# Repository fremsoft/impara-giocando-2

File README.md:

# impara-giocando-2
Seconda stagione di impara giocando, laboratorio di robotica e meccatronica
 
In questa directory verrà caricato tutto il materiale didattico che sviluppiamo nel corso del  laboratorio di robotica e meccatronica «impara giocando»

La playlist completa è disponibile in abbonamento a questo link: [Laboratorio di Robotica e Meccatronica](https://www.youtube.com/playlist?list=PLxAafib4pWc7ZTqss_0A76ByotfsSOVeD)

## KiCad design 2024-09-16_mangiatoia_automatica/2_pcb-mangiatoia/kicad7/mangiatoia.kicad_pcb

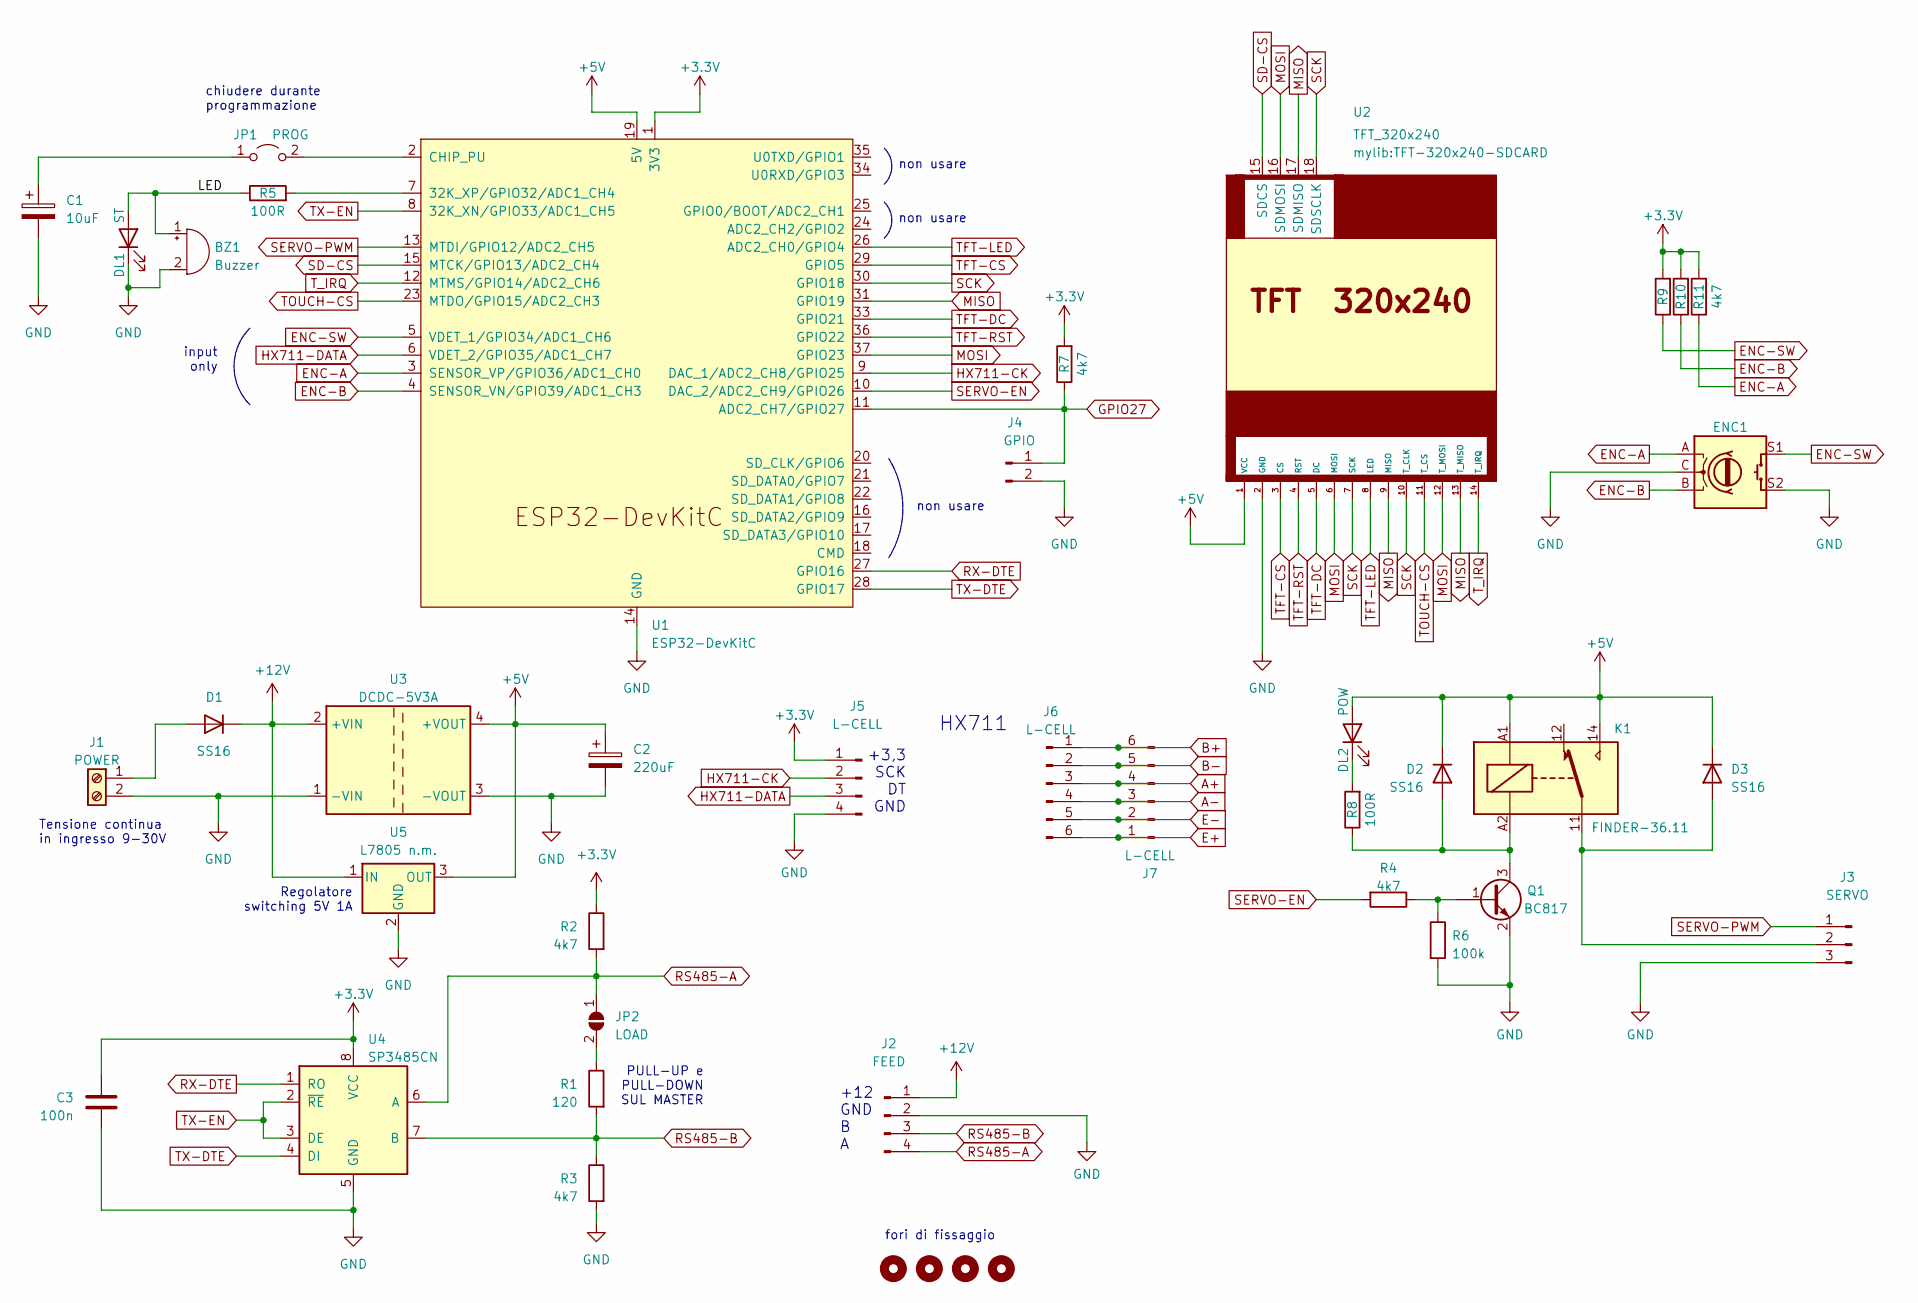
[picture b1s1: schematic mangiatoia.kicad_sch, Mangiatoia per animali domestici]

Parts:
BZ1: Buzzer; Buzzer_12x9.5RM7.6
C1: 10uF; CP_Radial_D6.3mm_P2.50mm
C2: 220uF; CP_Radial_D10.0mm_P5.00mm
C3: 100n; C_0603_1608Metric
D1, D2, D3: SS16; D_SMA
DL1: ST; LED_D5.0mm
DL2: POW; LED_0805_2012Metric
ENC1: RotaryEncoder_Switch; RotaryEncoder_Alps_EC11E-Switch_Vertical_H20mm
H1, H2, H3, H4: MountingHole; MountingHole_4.3mm_M4
J1: POWER; PhoenixContact_MSTBA_2,5_2-G-5,08_1x02_P5.08mm_Horizontal
J2: FEED; PinHeader_1x04_P2.54mm_Vertical
J3: SERVO; PinHeader_1x03_P2.54mm_Vertical
J4: GPIO; PinHeader_1x02_P2.54mm_Vertical
J5: L-CELL; PinHeader_1x04_P2.54mm_Vertical
J6: L-CELL; PinHeader_1x06_P2.54mm_Vertical
J7: L-CELL; TBL002A-350-06GR-2OR
JP1: PROG; PinHeader_1x02_P2.54mm_Vertical
JP2: LOAD; SolderJumper-2_P1.3mm_Open_RoundedPad1.0x1.5mm
K1: FINDER-36.11; Relay_SPDT_Finder_36.11
Q1: BC817; SOT-23
R1: 120; R_1206_3216Metric
R2, R3, R4: 4k7; R_0805_2012Metric; JLCPCB C304777
R5, R8: 100R; R_0805_2012Metric
R6: 100k; R_0805_2012Metric; JLCPCB C304777
R7, R9, R10, R11: 4k7; R_0805_2012Metric
U1: ESP32-DevKitC
U2: TFT_320x240; TFT-320x240-SDCARD
U3: DCDC-5V3A
U4: SP3485CN; SOIC-8_3.9x4.9mm_P1.27mm
U5: L7805 n.m.; TO-220-3_Vertical

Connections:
+3.3V: C3.1, J5.1, R2.1, R7.2, R9.2, R10.2, R11.2, U1.1 (3V3), U4.8 (VCC)
+5V: C2.1, D2.1 (K), D3.1 (K), DL2.2 (A), K1.14, K1.A1, U1.19 (5V), U2.1 (VCC), U3.4 (+VOUT), U5.3 (OUT)
+12V: D1.1 (K), J2.1, U3.2 (+VIN), U5.1 (IN)
/LED: BZ1.1 (-), DL1.2 (A), R5.1
A+: J6.3, J7.4
A-: J6.4, J7.3
B+: J6.1, J7.6
B-: J6.2, J7.5
E+: J6.6, J7.1
E-: J6.5, J7.2
ENC-A: ENC1.A, R11.1, U1.3 (SENSOR_VP/GPIO36/ADC1_CH0)
ENC-B: ENC1.B, R10.1, U1.4 (SENSOR_VN/GPIO39/ADC1_CH3)
ENC-SW: ENC1.S1, R9.1, U1.5 (VDET_1/GPIO34/ADC1_CH6)
GND: BZ1.2 (+), C1.2, C2.2, C3.2, DL1.1 (K), ENC1.C, ENC1.S2, J1.2, J2.2, J3.3, J4.2, J5.4, Q1.2 (E), R3.2, R6.2, U1.14 (GND), U1.32 (GND), U1.38 (GND), U2.2 (GND), U3.1 (-VIN), U3.3 (-VOUT), U4.5 (GND), U5.2 (GND)
GPIO27: J4.1, R7.1, U1.11 (ADC2_CH7/GPIO27)
HX711-CK: J5.2, U1.9 (DAC_1/ADC2_CH8/GPIO25)
HX711-DATA: J5.3, U1.6 (VDET_2/GPIO35/ADC1_CH7)
MISO: U1.31 (GPIO19), U2.9 (MISO), U2.13 (T_MISO), U2.17 (SDMISO)
MOSI: U1.37 (GPIO23), U2.6 (MOSI), U2.12 (T_MOSI), U2.16 (SDMOSI)
unnamed: D1.2 (A), J1.1
unnamed: D2.2 (A), K1.A2, Q1.3 (C), R8.1
unnamed: D3.2 (A), J3.2, K1.11
unnamed: DL2.1 (K), R8.2
unnamed: C1.1, JP1.1 (A)
unnamed: JP1.2 (B), U1.2 (CHIP_PU)
unnamed: JP2.2 (B), R1.1
unnamed: Q1.1 (B), R4.1, R6.1
unnamed: R5.2, U1.7 (32K_XP/GPIO32/ADC1_CH4)
RS485-A: J2.4, JP2.1 (A), R2.2, U4.6 (A)
RS485-B: J2.3, R1.2, R3.1, U4.7 (B)
RX-DTE: U1.27 (GPIO16), U4.1 (RO)
SCK: U1.30 (GPIO18), U2.7 (SCK), U2.10 (T_CLK), U2.18 (SDSCLK)
SD-CS: U1.15 (MTCK/GPIO13/ADC2_CH4), U2.15 (SDCS)
SERVO-EN: R4.2, U1.10 (DAC_2/ADC2_CH9/GPIO26)
SERVO-PWM: J3.1, U1.13 (MTDI/GPIO12/ADC2_CH5)
TFT-CS: U1.29 (GPIO5), U2.3 (CS)
TFT-DC: U1.33 (GPIO21), U2.5 (DC)
TFT-LED: U1.26 (ADC2_CH0/GPIO4), U2.8 (LED)
TFT-RST: U1.36 (GPIO22), U2.4 (RST)
TOUCH-CS: U1.23 (MTDO/GPIO15/ADC2_CH3), U2.11 (T_CS)
TX-DTE: U1.28 (GPIO17), U4.4 (DI)
TX-EN: U1.8 (32K_XN/GPIO33/ADC1_CH5), U4.2 (~RE), U4.3 (DE)
T_IRQ: U1.12 (MTMS/GPIO14/ADC2_CH6), U2.14 (T_IRQ)

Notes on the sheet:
chiudere durante programmazione
+3,3 SCK DT GND
PULL-UP e PULL-DOWN SUL MASTER
non usare
+12 GND B A
HX711
input only
Regolatore switching 5V 1A
Tensione continua in ingresso 9-30V
fori di fissaggio

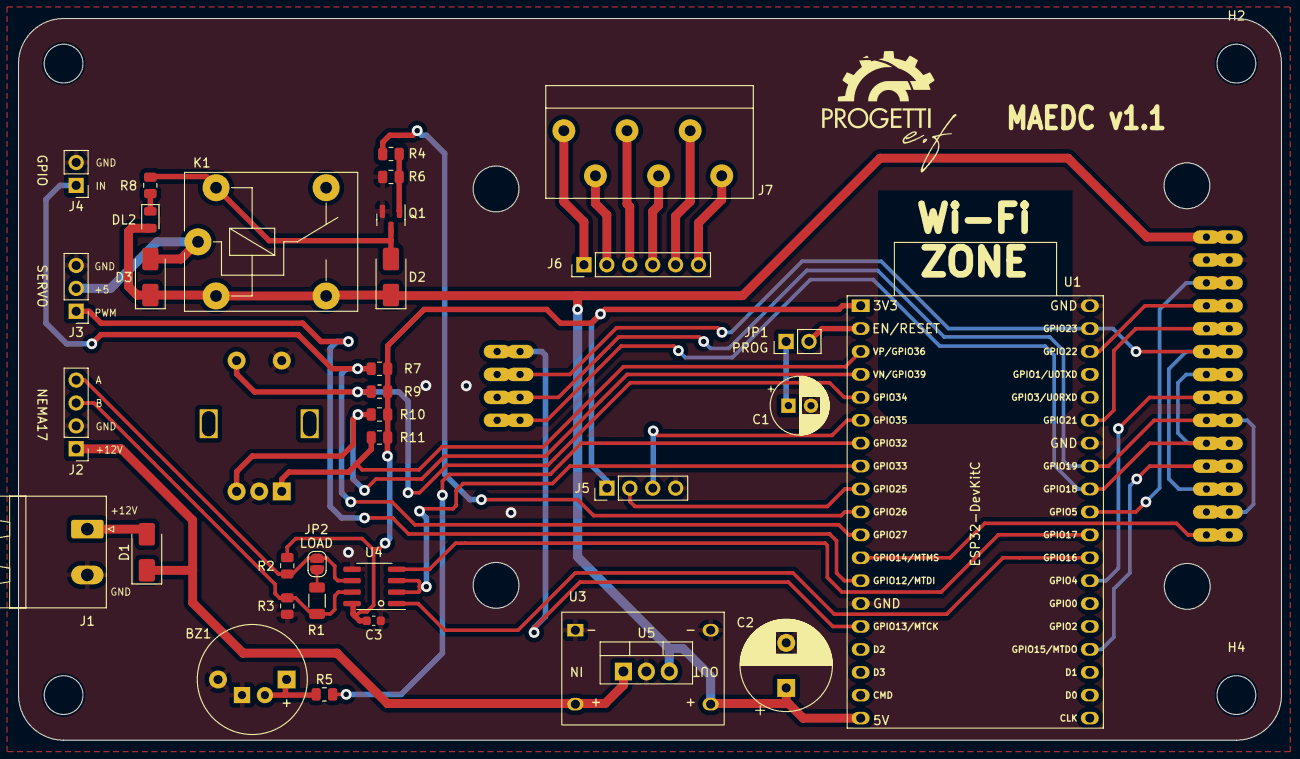
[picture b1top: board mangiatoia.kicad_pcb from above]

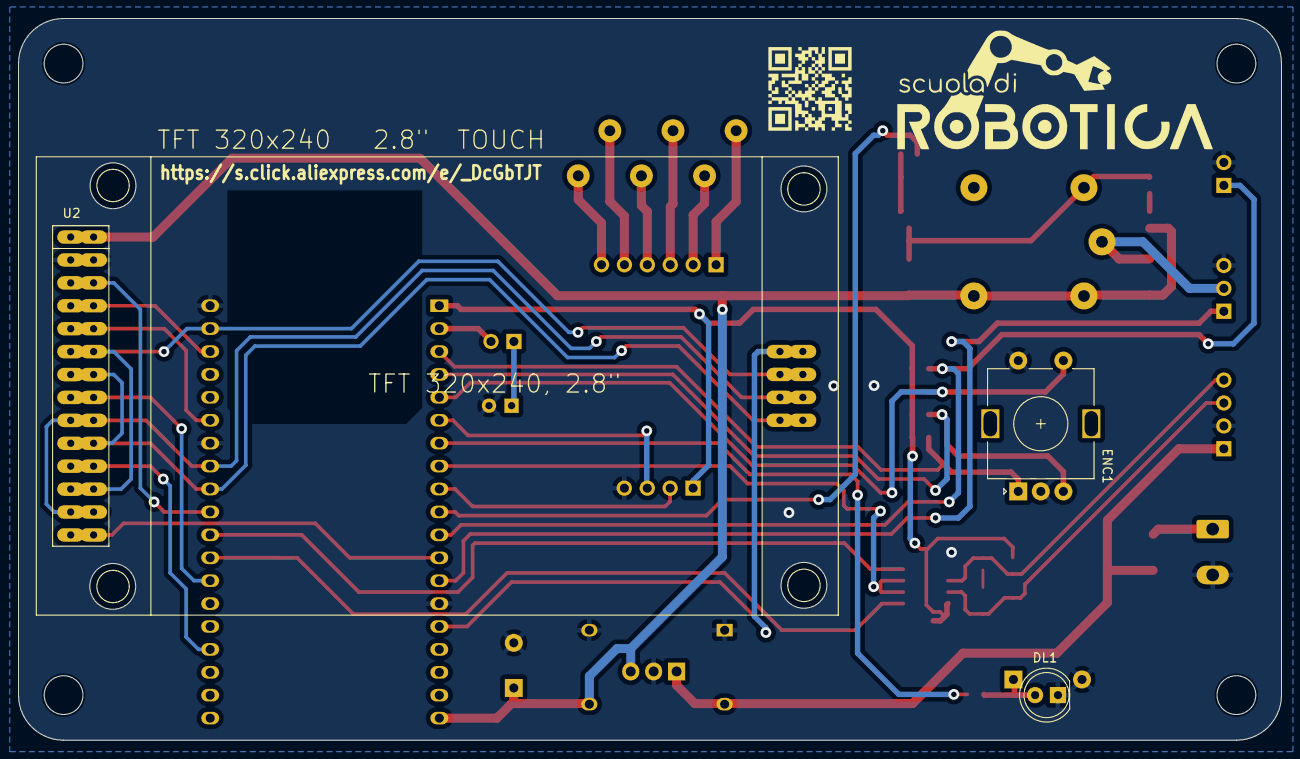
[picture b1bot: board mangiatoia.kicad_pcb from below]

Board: 2 copper layers, 140.0 x 80.0 mm, 41 parts (3 on the bottom side), 43 nets.

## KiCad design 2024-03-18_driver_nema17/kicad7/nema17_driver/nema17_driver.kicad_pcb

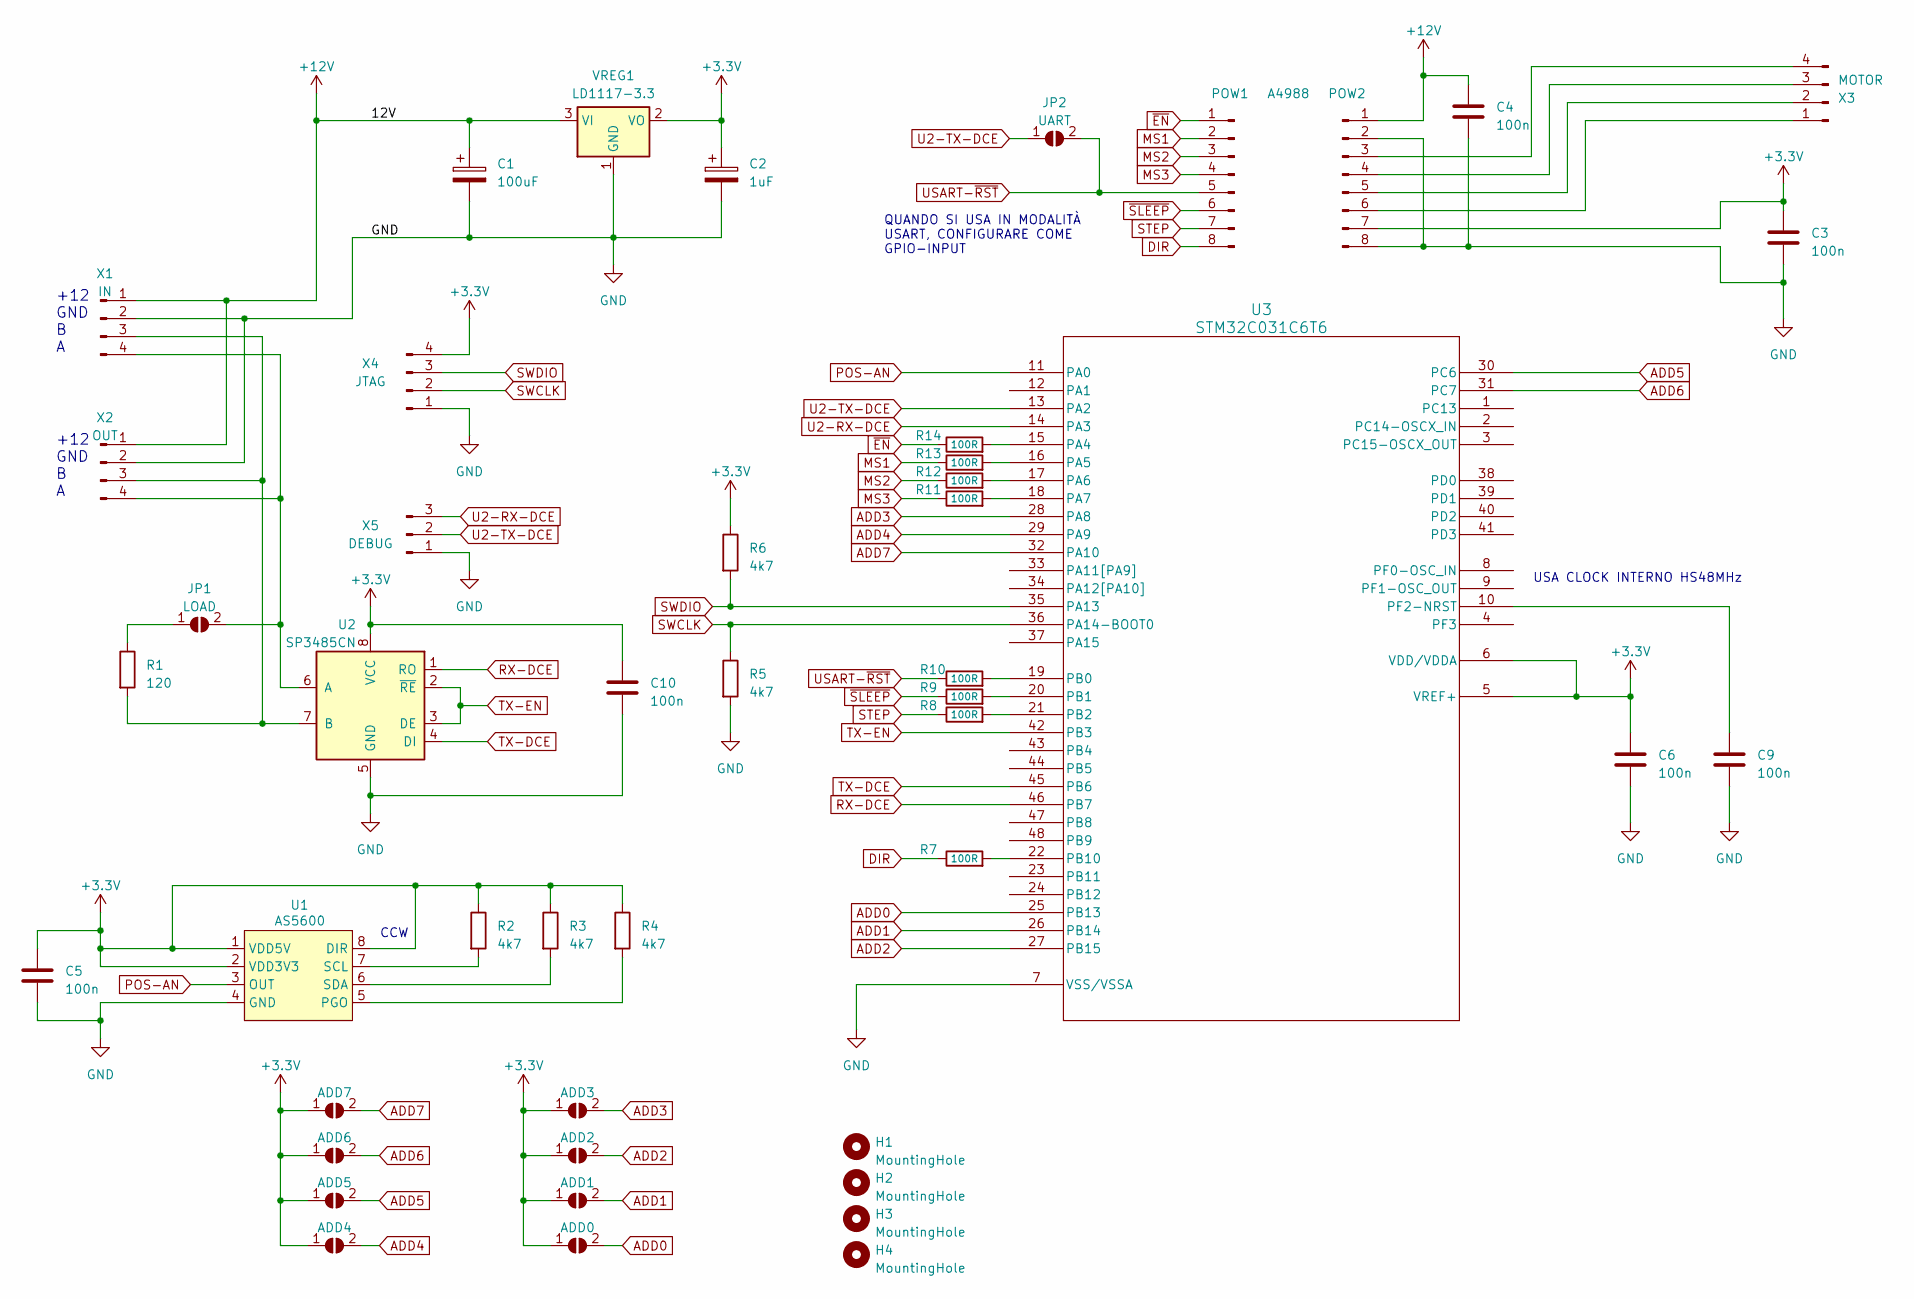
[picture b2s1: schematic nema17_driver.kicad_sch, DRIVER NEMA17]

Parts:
C1: 100uF; CP_Elec_6.3x7.7
C2: 1uF; CP_Elec_4x5.3
C3, C4, C5, C6, C9, C10: 100n; C_0603_1608Metric
H1, H2, H3, H4: MountingHole; MountingHole_3.5mm
JP1: LOAD; SolderJumper-2_P1.3mm_Open_RoundedPad1.0x1.5mm
JP2: UART; SolderJumper-2_P1.3mm_Open_RoundedPad1.0x1.5mm
JP3: ADD7; SolderJumper-2_P1.3mm_Open_RoundedPad1.0x1.5mm
JP4: ADD6; SolderJumper-2_P1.3mm_Open_RoundedPad1.0x1.5mm
JP5: ADD5; SolderJumper-2_P1.3mm_Open_RoundedPad1.0x1.5mm
JP6: ADD4; SolderJumper-2_P1.3mm_Open_RoundedPad1.0x1.5mm
JP7: ADD3; SolderJumper-2_P1.3mm_Open_RoundedPad1.0x1.5mm
JP8: ADD2; SolderJumper-2_P1.3mm_Open_RoundedPad1.0x1.5mm
JP9: ADD1; SolderJumper-2_P1.3mm_Open_RoundedPad1.0x1.5mm
JP10: ADD0; SolderJumper-2_P1.3mm_Open_RoundedPad1.0x1.5mm
POW1: A4988; PinSocket_1x08_P2.54mm_Vertical
POW2: Conn_01x08_Pin; PinSocket_1x08_P2.54mm_Vertical
R1: 120; R_1206_3216Metric
R2, R3, R4, R5, R6: 4k7; R_0603_1608Metric
R7, R8, R9, R10, R11, R12, R13, R14: 100R; R_0603_1608Metric
U1: AS5600; SO-8_3.9x4.9mm_P1.27mm
U2: SP3485CN; SOIC-8_3.9x4.9mm_P1.27mm
U3: STM32C031C6T6; LQFP48-7x7mm_STM
VREG1: LD1117-3.3; SOT-223-3_TabPin2
X1: IN; PinHeader_1x04_P2.54mm_Vertical
X2: OUT; PinHeader_1x04_P2.54mm_Vertical
X3: MOTOR; TBL002A-350-04GR-2OR
X4: JTAG; PinHeader_1x04_P2.54mm_Vertical
X5: DEBUG; PinHeader_1x03_P2.54mm_Vertical

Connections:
+3.3V: C2.1, C3.1, C5.1, C6.1, C10.1, JP3.1 (A), JP4.1 (A), JP5.1 (A), JP6.1 (A), JP7.1 (A), JP8.1 (A), JP9.1 (A), JP10.1 (A), POW2.7, R2.1, R3.1, R4.1, R6.1, U1.1 (VDD5V), U1.2 (VDD3V3), U1.8 (DIR), U2.8 (VCC), U3.5 (VREF+), U3.6 (VDD/VDDA), VREG1.2 (VO), X4.4
+12V: C1.1, C4.1, POW2.1, VREG1.3 (VI), X1.1, X2.1
ADD0: JP10.2 (B), U3.25 (PB13)
ADD1: JP9.2 (B), U3.26 (PB14)
ADD2: JP8.2 (B), U3.27 (PB15)
ADD3: JP7.2 (B), U3.28 (PA8)
ADD4: JP6.2 (B), U3.29 (PA9)
ADD5: JP5.2 (B), U3.30 (PC6)
ADD6: JP4.2 (B), U3.31 (PC7)
ADD7: JP3.2 (B), U3.32 (PA10)
DIR: POW1.8, R7.1
GND: C1.2, C2.2, C3.2, C4.2, C5.2, C6.2, C9.2, C10.2, POW2.2, POW2.8, R5.2, U1.4 (GND), U2.5 (GND), U3.7 (VSS/VSSA), VREG1.1 (GND), X1.2, X2.2, X4.1, X5.1
MS1: POW1.2, R13.1
MS2: POW1.3, R12.1
MS3: POW1.4, R11.1
unnamed: JP1.1 (A), R1.1
unnamed: JP1.2 (B), U2.6 (A), X1.4, X2.4
unnamed: POW2.3, X3.4
unnamed: POW2.4, X3.3
unnamed: POW2.5, X3.2
unnamed: POW2.6, X3.1
unnamed: R4.2, U1.5 (PGO)
unnamed: R2.2, U1.7 (SCL)
unnamed: R3.2, U1.6 (SDA)
unnamed: R1.2, U2.7 (B), X1.3, X2.3
unnamed: R14.2, U3.15 (PA4)
unnamed: R13.2, U3.16 (PA5)
unnamed: R12.2, U3.17 (PA6)
unnamed: R11.2, U3.18 (PA7)
unnamed: R10.2, U3.19 (PB0)
unnamed: R9.2, U3.20 (PB1)
unnamed: R8.2, U3.21 (PB2)
unnamed: R7.2, U3.22 (PB10)
unnamed: C9.1, U3.10 (PF2-NRST)
POS-AN: U1.3 (OUT), U3.11 (PA0)
RX-DCE: U2.1 (RO), U3.46 (PB7)
STEP: POW1.7, R8.1
SWCLK: R5.1, U3.36 (PA14-BOOT0), X4.2
SWDIO: R6.2, U3.35 (PA13), X4.3
TX-DCE: U2.4 (DI), U3.45 (PB6)
TX-EN: U2.2 (~RE), U2.3 (DE), U3.42 (PB3)
U2-RX-DCE: U3.14 (PA3), X5.3
U2-TX-DCE: JP2.1 (A), U3.13 (PA2), X5.2
USART-~RST: JP2.2 (B), POW1.5, R10.1
~EN: POW1.1, R14.1
~SLEEP: POW1.6, R9.1

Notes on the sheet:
CCW
+12 GND B A
+12 GND B A
QUANDO SI USA IN MODALITÀ USART, CONFIGURARE COME GPIO-INPUT
USA CLOCK INTERNO HS48MHz

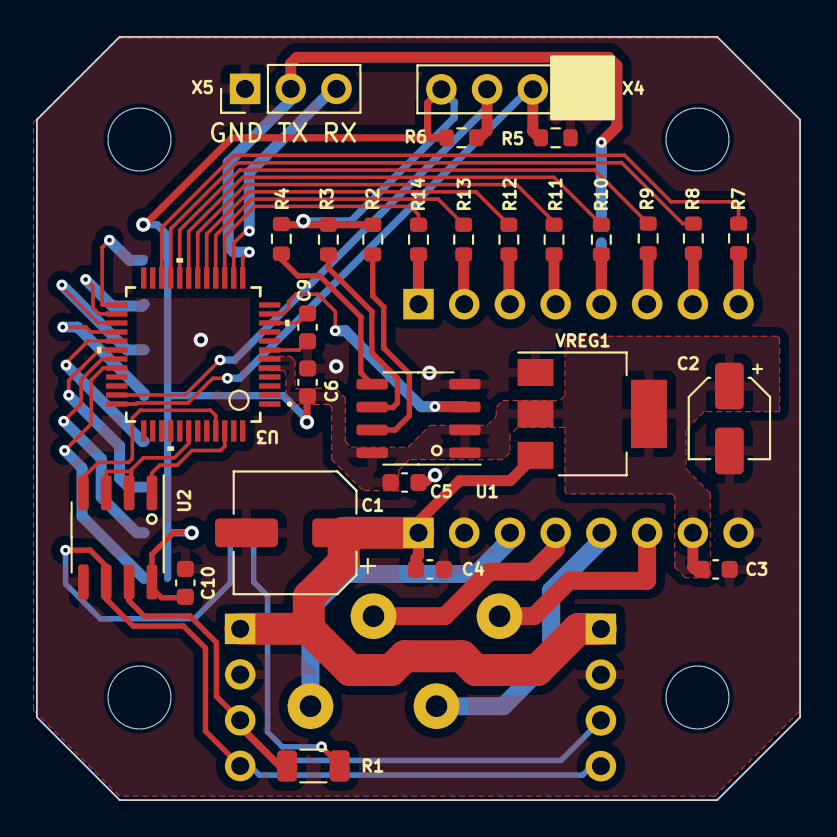
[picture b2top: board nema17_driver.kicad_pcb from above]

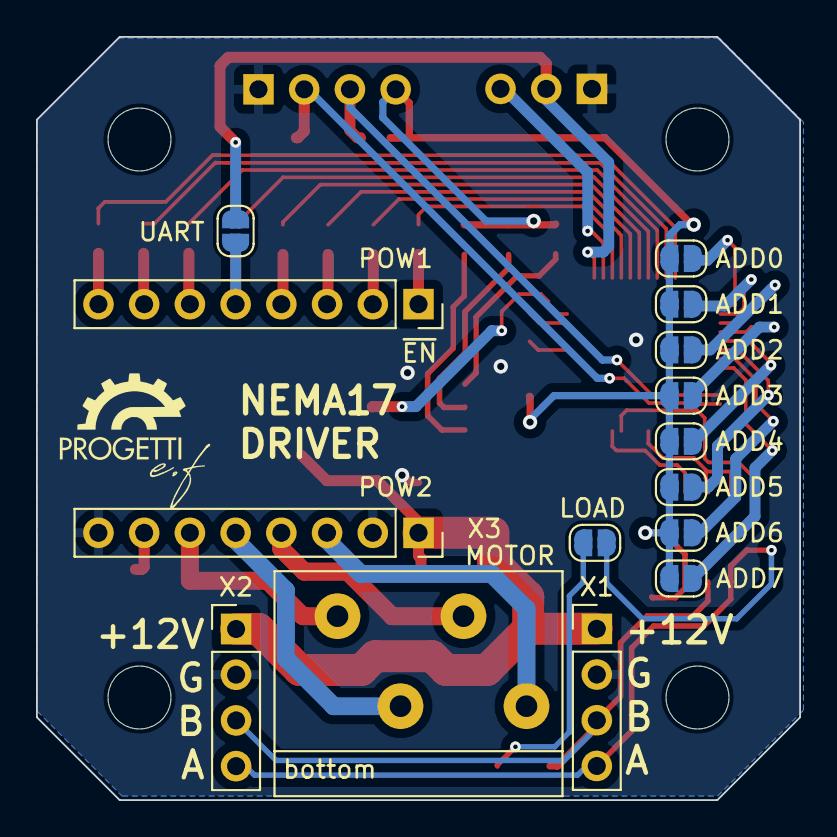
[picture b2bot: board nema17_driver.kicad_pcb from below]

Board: 2 copper layers, 42.4 x 42.4 mm, 47 parts (15 on the bottom side), 46 nets.

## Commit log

2022-10-17 Download SunFounder Tools
2022-10-17 Montaggio
2022-10-24 Movimento Rollarm Corretto
2022-11-14 Coordinate Polari-Rettangolari
2022-11-14 Fusion360
2022-11-21 Cinematica Inversa
2022-12-12 Approssimazioni successive
2022-12-19 Traiettoria
2023-01-09 SPLINE HERMITE NATURALE
2023-01-23 Catmull-Rom
2023-01-30 RETI NEURALI
2023-02-13 Neural Network PROGMEM
2023-02-27 Rete Neurale Ok
    I sorgenti riportano il codice eseguibile funzionante per calcolare la cinematica inversa per Robot RollArm con Arduino UNO e la libreria NeuralNetwork.h modificata
2023-03-13 Scanner 3D con Sonar
2023-05-15 FREQUENZIMETRO
    La sessione di laboratorio di oggi:
    https://youtube.com/live/Dy4e-h8nebQ
2023-06-05 BOZZA FIRMWARE FREQUENZIMETRO
2023-06-12 Debug e reverse engineering
2023-06-25 Programma completo
2023-06-25 Automazione carro allegorico
2023-06-26 versione con spline
2023-06-27 Bug Fix
2023-07-24 MH Electronics Motor Shield
2023-07-31 Libreria Fusion360
2023-08-21 Misura velocità ruote
2023-08-28 CONTROLLO VELOCITA PARTE 2
2023-09-04 correzioni
2023-09-04 SONAR
2023-09-11 Guida autonoma
2023-09-18 GUIDA AUTONOMA SMART CAR
2023-09-19 Massima velocità e precisione
2023-09-23 definitivo
2023-10-02 COMANDI SERIALI
2023-10-16 Multitasking ruote+sonar
2023-11-06 ESP32-CAM Primi Passi
2023-11-06 Rename readme.txt to read.me
2023-11-06 Rename read.me to readme.txt
2023-11-06 Rename readme.txt to README.txt
2023-11-06 differenze
2023-11-06 correzione
2023-11-06 prova a 20MHz
2023-11-20 Object Detection (deterministico)
2023-12-04 Object Detection con Edge Impulse
2023-12-18 Lettura cartelli stradali
2024-01-08 GO GO GO !!!
2024-01-22 supporto esp32-cam
2024-03-25 Schema di principio
2024-04-08 Posizionamento componenti
2024-04-15 Gerber
2024-05-20 Closed Loop Control
2024-05-27 debug
2024-09-02 distanziale
2024-09-16 mangiatoia automatica
2024-09-28 MAEDC v1.0
2024-09-30 coclea
2024-10-07 hx711
2024-11-04 TEST PCB
2024-11-06 v1.1
2024-11-11 TFT Bilancia
2024-11-18 collaudo generale
2024-11-25 debug 485
2024-11-25 programmazione STM32 driver Nema17
2024-11-27 riduttore epicicloidale
2024-12-02 tolleranze
2025-01-25 silos e scivolo
2025-01-31 corretto ingranaggio
2025-02-05 Heap meter
2025-02-05 memory heap
2025-02-06 inserito logo
2025-02-06 upgrade e aggiunta logo
2025-02-07 minime correzioni
2025-02-10 aggiunto gestione memoria non volatile e NTP
2025-02-10 imbastitura plan
2025-02-24 24 feb 2025
2025-02-24 24 febbraio
2025-03-03 2025-03-03
2025-03-17 2025-03-17
2025-03-25 Update LICENSE
2025-03-31 31 marzo 2025
2025-04-07 NTP con ora legale automatica
2025-04-11 send mail esp32
2025-04-14 email
2025-05-12 Dati dinamici in PHP
2025-05-25 comando via web
2025-05-26 AJAX
2025-06-19 RemoteXY
